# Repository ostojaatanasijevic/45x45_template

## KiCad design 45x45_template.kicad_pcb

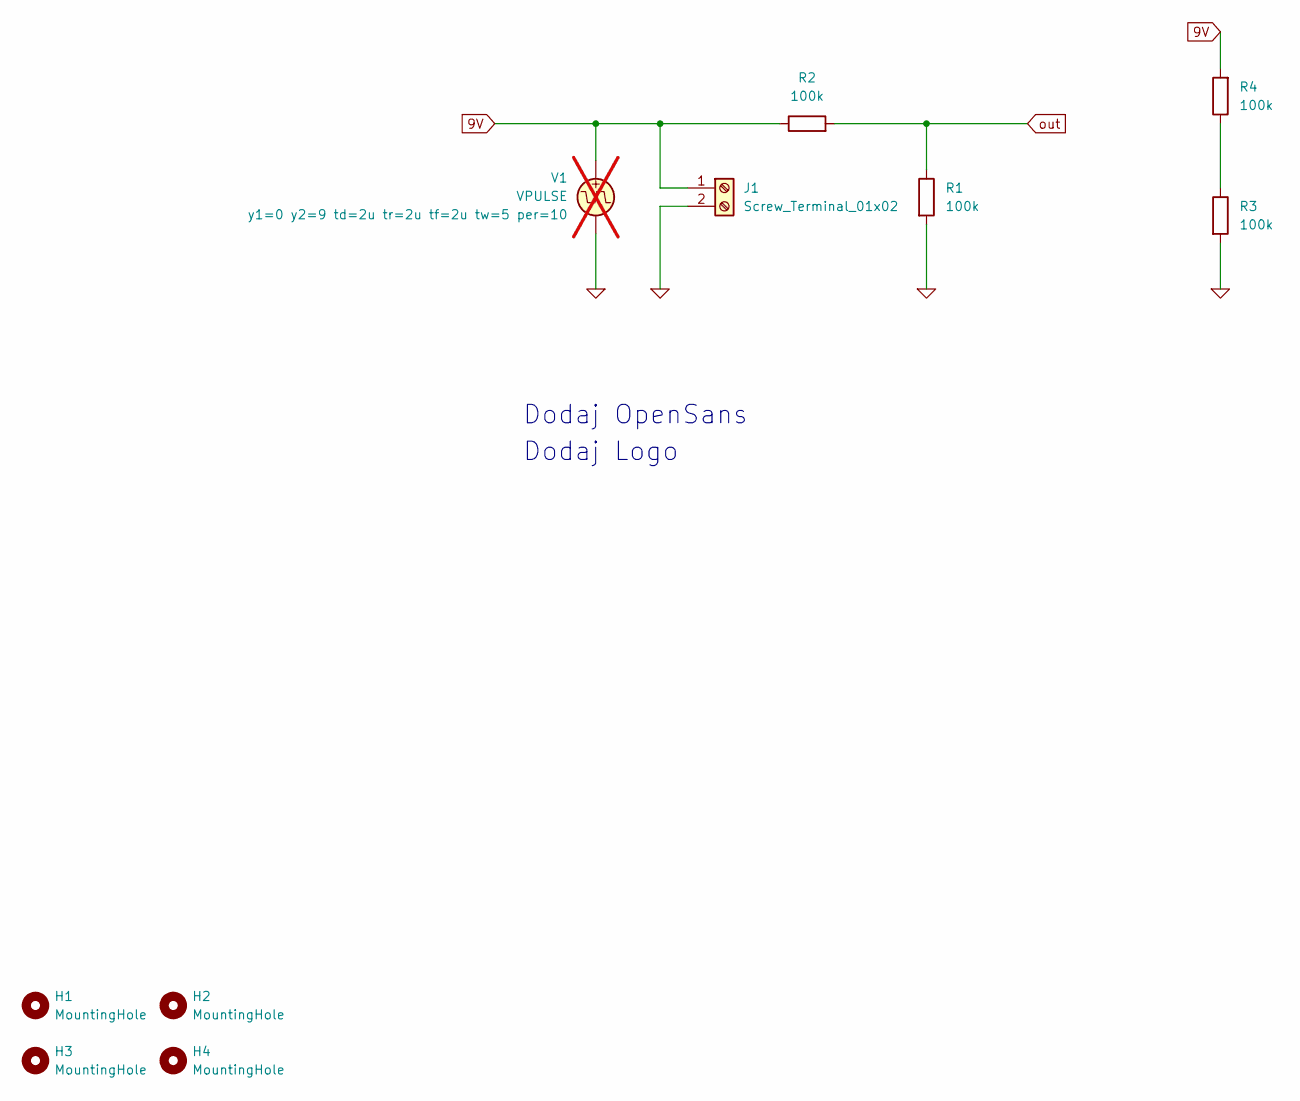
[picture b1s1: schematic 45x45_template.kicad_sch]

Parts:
H1, H2, H3, H4: MountingHole; MountingHole_3.2mm_M3_ISO14580_Pad_TopBottom
J1: Screw_Terminal_01x02; TerminalBlock_Phoenix_MKDS-1,5-2-5.08_1x02_P5.08mm_Horizont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
R1, R2: 100k; R_1206_3216Metric_Pad1.30x1.75mm_HandSolder
R3, R4: 100k; R_Axial_DIN0207_L6.3mm_D2.5mm_P15.24mm_Horizontal
V1: VPULSE; not fitted

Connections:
0: J1.2, R1.2, R3.2, V1.2
9V: J1.1, R2.1, R4.2, V1.1
unnamed: R3.1, R4.1
out: R1.1, R2.2

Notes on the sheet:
Dodaj OpenSans
Dodaj Logo

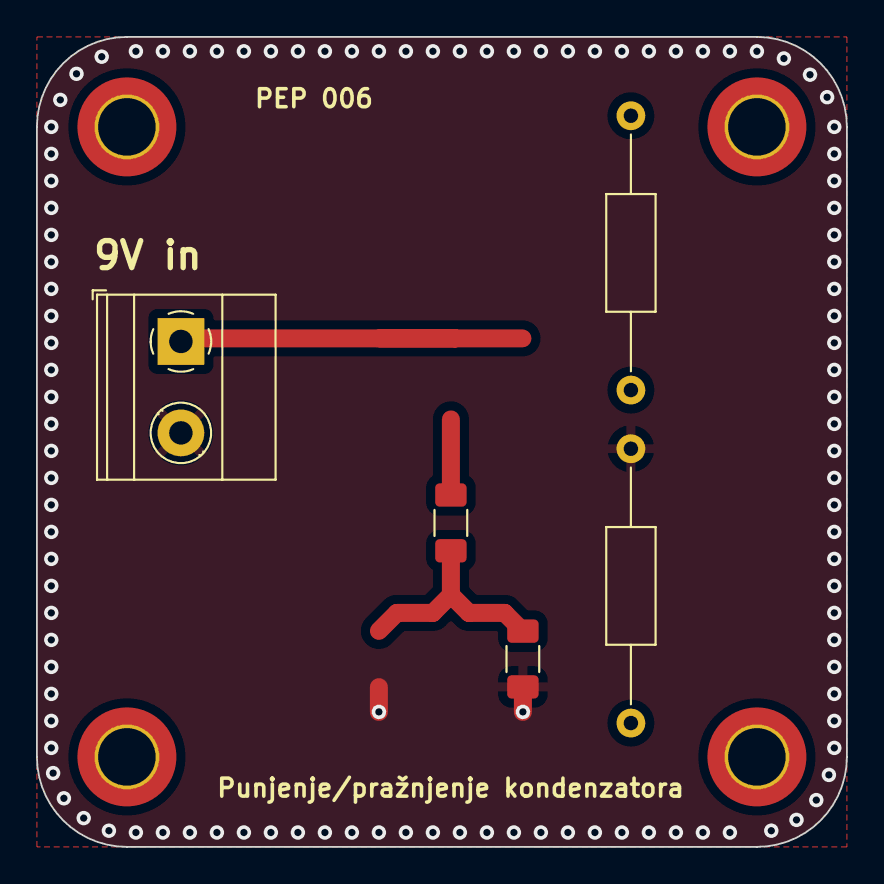
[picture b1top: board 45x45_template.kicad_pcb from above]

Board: 2 copper layers, 45.0 x 45.0 mm, 9 parts (0 on the bottom side), 4 nets.

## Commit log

2024-11-21 Init.
